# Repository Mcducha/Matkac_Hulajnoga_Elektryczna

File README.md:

# Matkac_Hulajnoga_Elektryczna
Projekt Technika Mikroprocesorowa

,,Matkac-Hulajnoga Elektryczna”

Grupa Elektroniki Morskiej sem.5

Rok akademicki 2022/2023

Skład zespołu;

1.Magdalena Borowiec   
2.Mateusz Aniołkowski  
3.Oskar Wawrzyniak    
4.Grzegorz Grzenkowicz  
5.Dennis Ahmed         
6.Kacper Wróblewski    
7.Dawid Sanecki 

Założenia projektowe;

•	Trzy tryby pracy

-	Zwykły

-	Z ograniczeniem mocy

-	Z ograniczeniem prędkości

•	Oświetlenie drogowe

•	Prędkościomierz (opcjonalnie)

•	Płynna regulacja prędkości

•	System monitorowania i zabezpieczenia baterii

•	Amperometryka silnika

•	Kontrola temperatury na poszczególnych podzespołach (opcjonalnie)

Etapy naszej pracy przedstawia:

<a href="https://miro.com/app/board/uXjVPJqmcqU=/">Miro projektu</a>

Zestawienie materiałowe:

      Poziom 0 (produkt gotowy)        Poziom 1 (części podstawowe/komponenty)      Poziom 2 (części dodatkowe/podzespoły)          
               Hulajnoga(1szt.)	                              Koło (1szt.)	               Wyświetlacz OLED(1szt.)
	                                                         Kierownica(1szt.)	          Przetwornica napięcia(1szt.)
	                                                              Rama (1szt.)	                      Lampa LED(1szt.)
	                                                        Koło silnik(1szt.)	                      Hallotron(1szt.)
	                                                  Sterownik silnika(1szt.)	                        Arduino(1szt.)
	                                                            Bateria(1szt.)	                     Płytka PCB(1szt.)
	                                                       Manetka gazu(1szt.)	                     Kontaktron(1szt.)
		                                                                                            Złącza ARK(20szt.)

Opis projektu:

Przetwornica napięciowa step down  reguluje napięcie dostarczane na Arduino. Na  kierownicy umieszczano manetkę gazu, do  której dołączamy wyświetlacz OLED sterowany za pomocą Arduino  , podłączenie za pomocą złączy ARK. Przełączanie manetki gazu, jak również hamulca i hallotronu(umieszczonego w przednim kole hulajnogi) jest realizowane za pomocą przycisków. Aby zapobiec  drganiom styków podczas przełączania zastosowano debouncing, realizowany przez dodatkowy rezystor oraz komendę PULLUP w komunikacji z arduino. Na kierownicy umieszczono również lampę LED, sterowaną Arduino , napięcie dostarczane do lamp jest regulowane przez dwa tranzystory Mosfet. Na wyjściu z baterii umieszczono dzielnik napięcia w celu zredukowania napięcia  z 42V do 5V. Czujnik prędkości zrealizowano za pomocą kontaktronu umieszczono w tylnim kole hulajnogi, który umożliwia zliczanie obrotów koła, informacje dostarczone do Arduino przeliczamy i wyświetlamy na wyświetlaczu OLED jako informacja o prędkości  jazdy.

Testy przeprowadzone przez Mateusza wykazały skuteczność zastosowanych rozwiązań:

<a href="https://github.com/Mcducha/Matkac_Hulajnoga_Elektryczna/tree/main/Testy">testhulajnogi</a>

W projekcie zrealizowano:

•	oświetlenie drogowe

•	prędkościomierz

•	płynna regulacja prędkości

Z początkowych założeń nie udało  się zrealizować :

•	Trzy tryby pracy

-	Zwykły

-	Z ograniczeniem mocy

-	Z ograniczeniem prędkości

•	System monitorowania i zabezpieczenia baterii

•	Amperometryka silnika

•	Kontrola temperatury na poszczególnych podzespołach

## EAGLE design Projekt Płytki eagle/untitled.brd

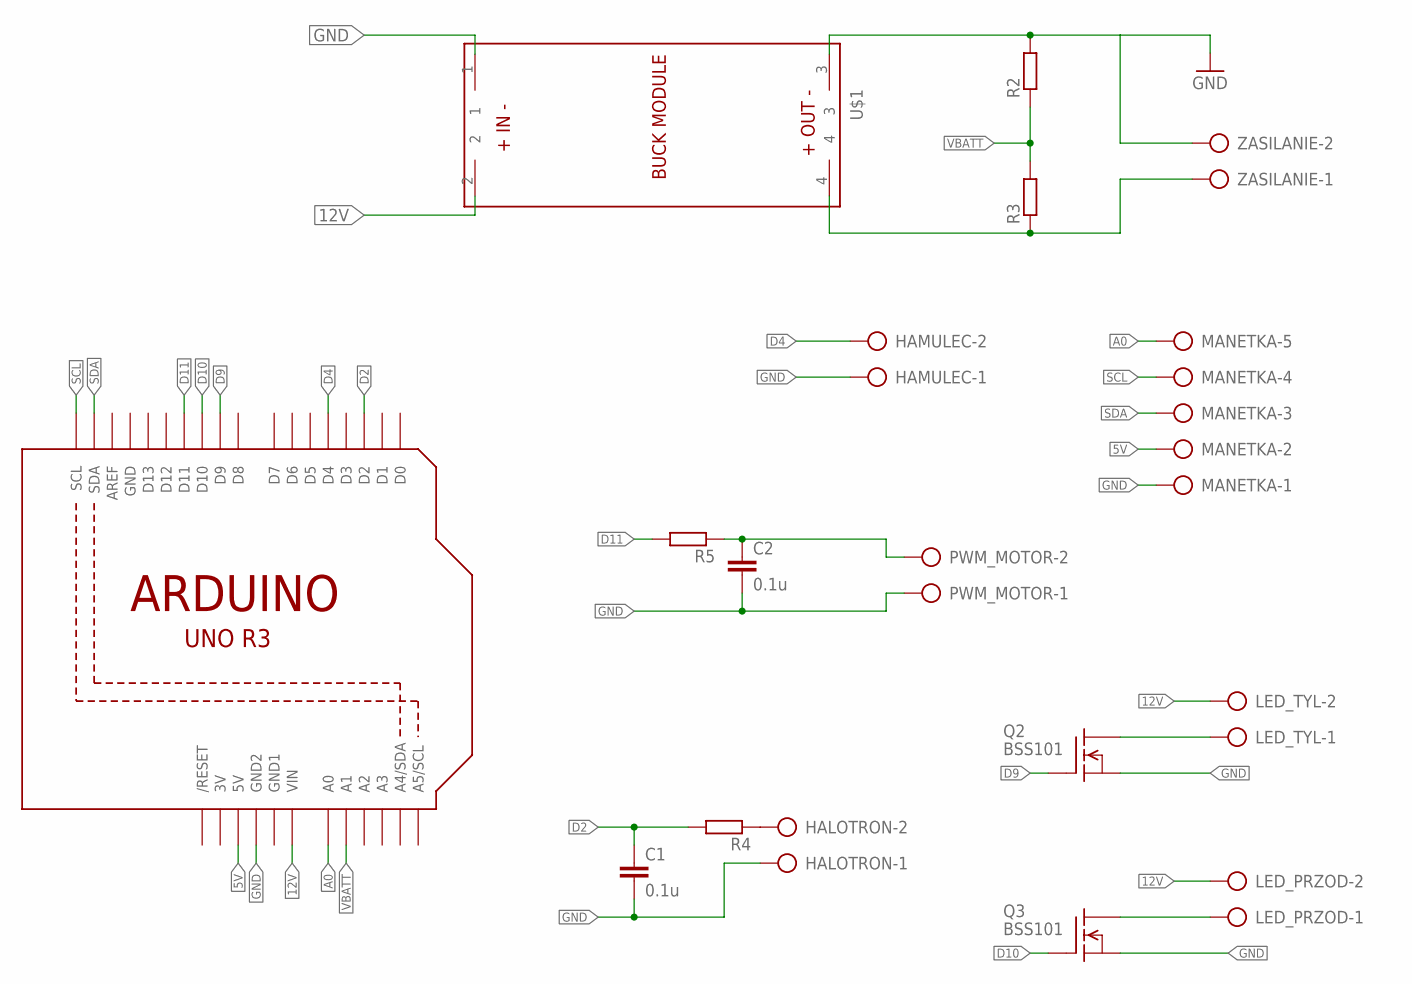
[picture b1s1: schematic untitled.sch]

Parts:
C1, C2: 0.1u; C025-025X050
HALOTRON: AK500/2-H
HAMULEC: AK500/2-H
LED_PRZOD: AK500/2-H
LED_TYL: AK500/2-H
MANETKA: AK300/5
PWM_MOTOR: AK500/2-H
Q1: ARDUINOR3-NOIOREF-NOTEXT; ARDUINOR3-NOTEXT-NOIOREF
Q2, Q3: BSS101; TO92
R2, R3, R4, R5: R-EU_0204/7; 0204/7
U$1: BUCK_MODULEWITH_SMDPADS&THROUGHHOLES; BUCK_MODULE
ZASILANIE: AK500/2-H

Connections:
3V: Q1.3V
5V: MANETKA.2, Q1.5V
12V: LED_PRZOD.2, LED_TYL.2, Q1.VIN, U$1.2
A0: MANETKA.5, Q1.A0
D2: C1.1, Q1.D2, R4.2
D4: HAMULEC.2, Q1.D4
D9: Q1.D9, Q2.2 (G)
D10: Q1.D10, Q3.2 (G)
D11: Q1.D11, R5.2
GND: C1.2, C2.2, HALOTRON.1, HAMULEC.1, MANETKA.1, PWM_MOTOR.1, Q1.GND2, Q2.1 (S), Q3.1 (S), U$1.1
GND1: Q1.GND1
unnamed: Q1.GND, R2.2, U$1.3, ZASILANIE.2
unnamed: HALOTRON.2, R4.1
unnamed: R3.1, U$1.4, ZASILANIE.1
unnamed: C2.1, PWM_MOTOR.2, R5.1
unnamed: LED_TYL.1, Q2.3 (D)
unnamed: LED_PRZOD.1, Q3.3 (D)
SCL: MANETKA.4, Q1.SCL
SDA: MANETKA.3, Q1.SDA
VBATT: Q1.A1, R2.1, R3.2

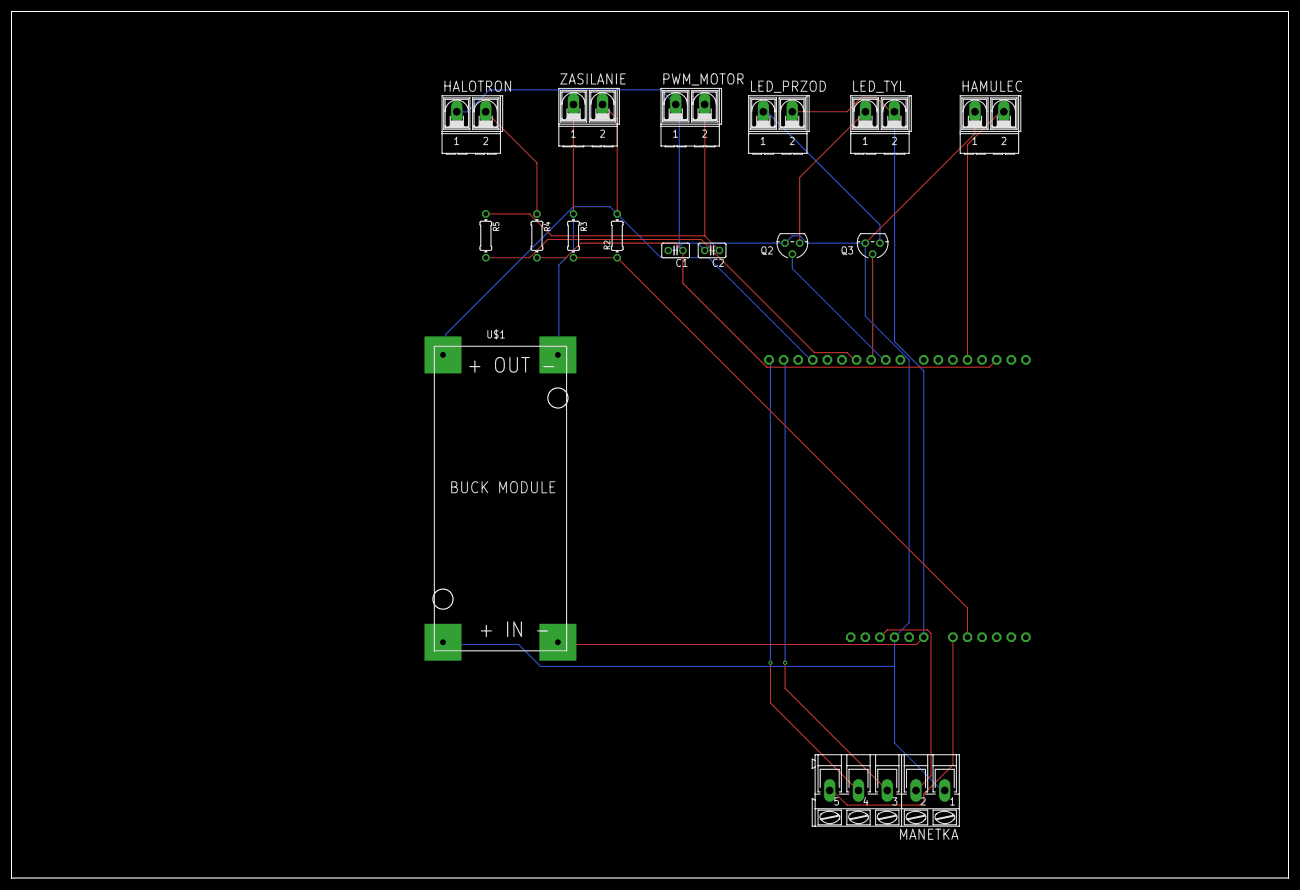
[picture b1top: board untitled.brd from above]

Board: 2 copper layers, 222.2 x 150.8 mm, 17 parts (0 on the bottom side), 18 nets.

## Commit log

2023-02-12 logo
2023-02-12 biblioteki
2023-02-12 Rename README.md to sprawozdanie.md
2023-02-12 Rename sprawozdanie.md to README.md
